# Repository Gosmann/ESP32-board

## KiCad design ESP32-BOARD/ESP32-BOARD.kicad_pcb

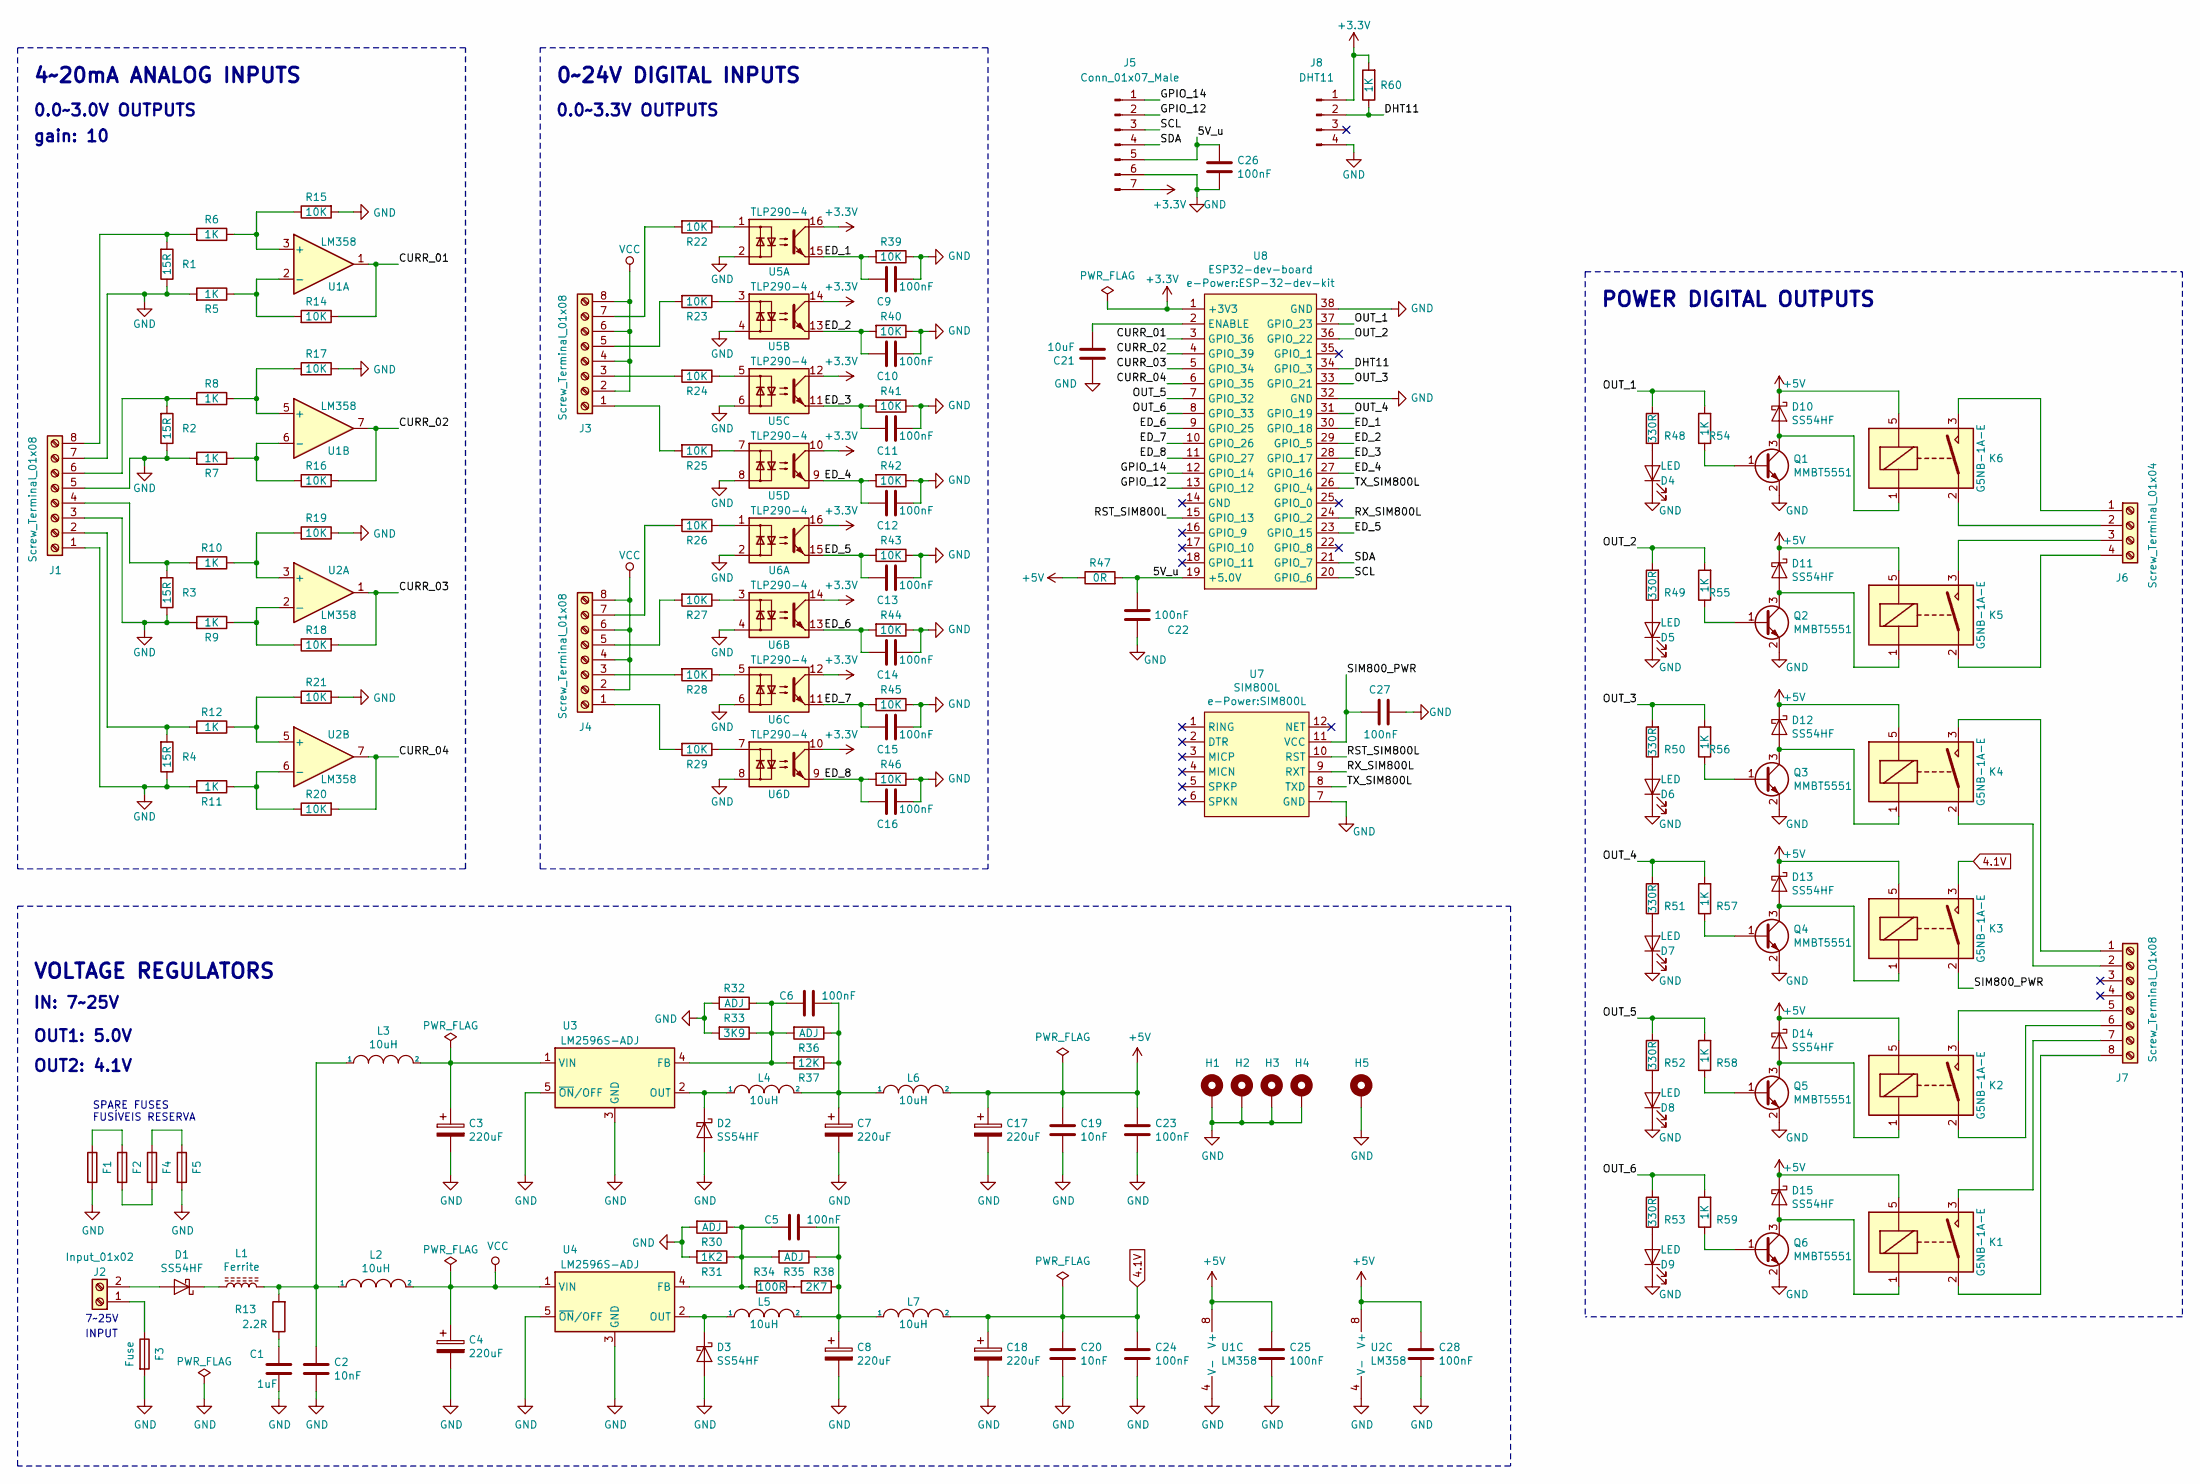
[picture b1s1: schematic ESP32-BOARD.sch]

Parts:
C1: 1uF; C_0805_2012Metric; LCSC C28323
C2, C19, C20: 10nF; C_0805_2012Metric; LCSC C1710
C3, C4, C7, C8, C17, C18: 220uF; CP_Elec_8x10; LCSC C311611
C5, C6, C9, C10, C11, C12, C13, C14, C15, C16, C22, C23, C24, C25, C26, C27, C28: 100nF; C_0805_2012Metric; LCSC C49678
C21: 10uF; C_0805_2012Metric; LCSC C15850
D1, D2, D3, D10, D11, D12, D13, D14, D15: SS54HF; DO-214AC; LCSC C22452
D4, D5, D6, D7, D8, D9: LED; LED_0805_2012Metric; LCSC C84256
F1, F2, F3, F4, F5: Fuse; FUSE_1206_3216Metric; LCSC C182445
H1, H2, H3, H4: MountingHole_Pad; MountingHole_4mm_Pad_Via
H5: MountingHole_Pad; MountingHole_3.2mm_M3_Pad
J1, J3, J4, J7: Screw_Terminal_01x08; TerminalBlock_Phoenix_MKDS-1,5-8-5.08_1x08_P5.08mm_Horizont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
J2: Input_01x02; TerminalBlock_Phoenix_MKDS-1,5-2_1x02_P5.00mm_Horizontal
J5: Conn_01x07_Male; PinHeader_1x07_P2.54mm_Horizontal
J6: Screw_Terminal_01x04; TerminalBlock_Phoenix_MKDS-1,5-4-5.08_1x04_P5.08mm_Horizont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
J8: DHT11; PinHeader_1x04_P2.54mm_Vertical
K1, K2, K3, K4, K5, K6: G5NB-1A-E; Relay_SPST_Omron-G5Q-1A
L1: Ferrite; FB_0603_1608Metric; LCSC C1002
L2, L3, L4, L5, L6, L7: 10uH; L_10.4x10.4_H4.8; LCSC C9935
Q1, Q2, Q3, Q4, Q5, Q6: MMBT5551; SOT-23; LCSC C2145
R1, R2, R3, R4: 15R; R_0805_2012Metric; LCSC C17480
R5, R6, R7, R8, R9, R10, R11, R12, R54, R55, R56, R57, R58, R59, R60: 1K; R_0805_2012Metric; LCSC C17513
R13: 2.2R; R_0805_2012Metric; LCSC C17521
R14, R15, R16, R17, R18, R19, R20, R21, R22, R23, R24, R25, R26, R27, R28, R29, R39, R40, R41, R42, R43, R44, R45, R46: 10K; R_0805_2012Metric; LCSC C17414
R30, R32, R35, R36: ADJ; R_0805_2012Metric
R31: 1K2; R_0805_2012Metric; LCSC C17379
R33: 3K9; R_0805_2012Metric; LCSC C17614
R34: 100R; R_0805_2012Metric; LCSC C17408
R37: 12K; R_0805_2012Metric; LCSC C17444
R38: 2K7; R_0805_2012Metric; LCSC C17530
R47: 0R; R_0805_2012Metric; LCSC C17477
R48, R49, R50, R51, R52, R53: 330R; R_0805_2012Metric; LCSC C17630
U1, U2: LM358; SOIC-8_3.9x4.9mm_P1.27mm; LCSC C7950
U3, U4: LM2596S-ADJ; TO-263-5_TabPin3; LCSC C52684
U5, U6: TLP290-4; SOIC-16_4.55x10.3mm_P1.27mm(TLP290-4); LCSC C39031
U7: SIM800L
U8: ESP32-dev-board; ESP-32-dev-kit

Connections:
4.1V: C18.1, C20.1, C24.1, K3.3, L7.2
+3V3: J5.7, J8.1, R60.2, U5.10, U5.12, U5.14, U5.16, U6.10, U6.12, U6.14, U6.16, U8.1 (+3V3)
+5V: C17.1, C19.1, C23.1, C25.1, C28.1, D10.1 (K), D11.1 (K), D12.1 (K), D13.1 (K), D14.1 (K), D15.1 (K), K1.5, K2.5, K3.5, K4.5, K5.5, K6.5, L6.2, R47.1, U1.8 (V+), U2.8 (V+)
/5V_u: C22.2, C26.1, J5.5, R47.2, U8.19 (+5.0V)
/CURR_01: R14.1, U1.1, U8.3 (GPIO_36)
/CURR_02: R16.2, U1.7, U8.4 (GPIO_39)
/CURR_03: R18.2, U2.1, U8.5 (GPIO_34)
/CURR_04: R20.2, U2.7, U8.6 (GPIO_35)
/DHT11: J8.2, R60.1, U8.34 (GPIO_3)
/ED_1: C9.2, R39.2, U5.15, U8.30 (GPIO_18)
/ED_2: C10.2, R40.2, U5.13, U8.29 (GPIO_5)
/ED_3: C11.2, R41.2, U5.11, U8.28 (GPIO_17)
/ED_4: C12.2, R42.2, U5.9, U8.27 (GPIO_16)
/ED_5: C13.2, R43.2, U6.15, U8.23 (GPIO_15)
/ED_6: C14.2, R44.2, U6.13, U8.9 (GPIO_25)
/ED_7: C15.2, R45.2, U6.11, U8.10 (GPIO_26)
/ED_8: C16.2, R46.2, U6.9, U8.11 (GPIO_27)
/GPIO_12: J5.2, U8.13 (GPIO_12)
/GPIO_14: J5.1, U8.12 (GPIO_14)
/OUT_1: R48.2, R54.2, U8.37 (GPIO_23)
/OUT_2: R49.2, R55.2, U8.36 (GPIO_22)
/OUT_3: R50.2, R56.2, U8.33 (GPIO_21)
/OUT_4: R51.2, R57.2, U8.31 (GPIO_19)
/OUT_5: R52.2, R58.2, U8.7 (GPIO_32)
/OUT_6: R53.2, R59.2, U8.8 (GPIO_33)
/RST_SIM800L: U7.10 (RST), U8.15 (GPIO_13)
/RX_SIM800L: U7.9 (RXT), U8.24 (GPIO_2)
/SCL: J5.3, U8.20 (GPIO_6)
/SDA: J5.4, U8.21 (GPIO_7)
/SIM800_PWR: C27.1, K3.2, U7.11 (VCC)
/TX_SIM800L: U7.8 (TXD), U8.26 (GPIO_4)
GND: C1.2, C2.2, C3.2, C4.2, C7.2, C8.2, C9.1, C10.1, C11.1, C12.1, C13.1, C14.1, C15.1, C16.1, C17.2, C18.2, C19.2, C20.2, C21.1, C22.1, C23.2, C24.2, C25.2, C26.2, C27.2, C28.2, D2.2 (A), D3.2 (A), D4.1 (K), D5.1 (K), D6.1 (K), D7.1 (K), D8.1 (K), D9.1 (K), F1.2, F3.2, F5.2, H1.1, H2.1, H3.1, H4.1, H5.1, J1.1, J1.3, J1.5, J1.7, J5.6, J8.4, Q1.2 (E), Q2.2 (E), Q3.2 (E), Q4.2 (E), Q5.2 (E), Q6.2 (E), R1.1, R2.1, R3.1, R4.1, R5.2, R7.2, R9.2, R11.2, R15.2, R17.1, R19.1, R21.1, R30.2, R31.2, R32.2, R33.2, R39.1, R40.1, R41.1, R42.1, R43.1, R44.1, R45.1, R46.1, U1.4 (V-), U2.4 (V-), U3.3 (GND), U3.5 (~ON~/OFF), U4.3 (GND), U4.5 (~ON~/OFF), U5.2, U5.4, U5.6, U5.8, U6.2, U6.4, U6.6, U6.8, U7.7 (GND), U8.32 (GND), U8.38 (GND)
unnamed: C1.1, R13.1
unnamed: C2.1, L1.2, L2.1, L3.1, R13.2
unnamed: C3.1, L3.2, U3.1 (VIN)
unnamed: C5.1, C8.1, L5.2, L7.1, R35.1, R38.1
unnamed: C5.2, R30.1, R31.1, R34.2, R35.2, U4.4 (FB)
unnamed: C6.1, C7.1, L4.2, L6.1, R36.1, R37.1
unnamed: C6.2, R32.1, R33.1, R36.2, R37.2, U3.4 (FB)
unnamed: C21.2, U8.2 (ENABLE)
unnamed: D1.1 (K), L1.1
unnamed: D1.2 (A), J2.2
unnamed: D2.1 (K), L4.1, U3.2 (OUT)
unnamed: D3.1 (K), L5.1, U4.2 (OUT)
unnamed: D4.2 (A), R48.1
unnamed: D5.2 (A), R49.1
unnamed: D6.2 (A), R50.1
unnamed: D7.2 (A), R51.1
unnamed: D8.2 (A), R52.1
unnamed: D9.2 (A), R53.1
unnamed: D10.2 (A), K6.1, Q1.3 (C)
unnamed: D11.2 (A), K5.1, Q2.3 (C)
unnamed: D12.2 (A), K4.1, Q3.3 (C)
unnamed: D13.2 (A), K3.1, Q4.3 (C)
unnamed: D14.2 (A), K2.1, Q5.3 (C)
unnamed: D15.2 (A), K1.1, Q6.3 (C)
unnamed: F1.1, F2.1
unnamed: F2.2, F4.2
unnamed: F3.1, J2.1
unnamed: F4.1, F5.1
unnamed: J1.2, R4.2, R12.2
unnamed: J1.4, R3.2, R10.2
unnamed: J1.6, R2.2, R8.2
unnamed: J1.8, R1.2, R6.2
unnamed: J3.1, R25.2
unnamed: J3.3, R24.2
unnamed: J3.5, R23.2
unnamed: J3.7, R22.2
unnamed: J4.1, R29.2
unnamed: J4.3, R28.2
unnamed: J4.5, R27.2
unnamed: J4.7, R26.2
unnamed: J6.1, K6.3
unnamed: J6.2, K6.2
unnamed: J6.3, K5.3
unnamed: J6.4, K5.2
unnamed: J7.1, K4.3
unnamed: J7.2, K4.2
unnamed: J7.5, K2.3
unnamed: J7.6, K2.2
unnamed: J7.7, K1.3
unnamed: J7.8, K1.2
unnamed: Q1.1 (B), R54.1
unnamed: Q2.1 (B), R55.1
unnamed: Q3.1 (B), R56.1
unnamed: Q4.1 (B), R57.1
unnamed: Q5.1 (B), R58.1
unnamed: Q6.1 (B), R59.1
unnamed: R10.1, R19.2, U2.3 (+)
unnamed: R11.1, R20.1, U2.6 (-)
unnamed: R12.1, R21.2, U2.5 (+)
unnamed: R5.1, R14.2, U1.2 (-)
unnamed: R6.1, R15.1, U1.3 (+)
unnamed: R7.1, R16.1, U1.6 (-)
unnamed: R8.1, R17.2, U1.5 (+)
unnamed: R9.1, R18.1, U2.2 (-)
unnamed: R22.1, U5.1
unnamed: R23.1, U5.3
unnamed: R24.1, U5.5
unnamed: R25.1, U5.7
unnamed: R26.1, U6.1
unnamed: R27.1, U6.3
unnamed: R28.1, U6.5
unnamed: R29.1, U6.7
unnamed: R34.1, R38.2
VCC: C4.1, J3.2, J3.4, J3.6, J3.8, J4.2, J4.4, J4.6, J4.8, L2.2, U4.1 (VIN)

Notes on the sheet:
VOLTAGE REGULATORS
IN: 7~~25V
OUT1: 5.0V
OUT2: 4.1V
4~~20mA ANALOG INPUTS
0~~24V DIGITAL INPUTS
0.0~~3.3V OUTPUTS
POWER DIGITAL OUTPUTS
0.0~~3.0V OUTPUTS
gain: 10
INPUT
7~~25V
SPARE FUSES FUSÍVEIS RESERVA

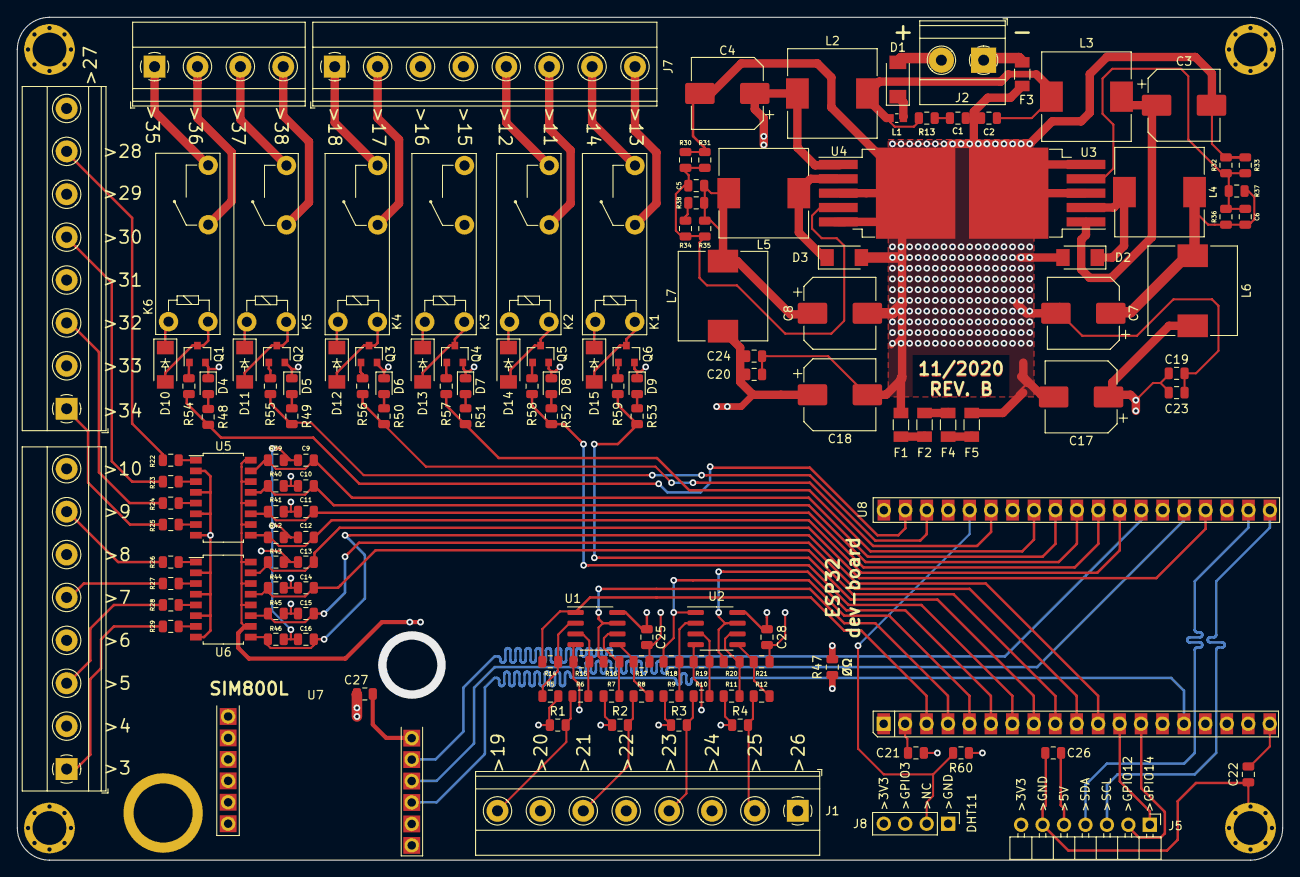
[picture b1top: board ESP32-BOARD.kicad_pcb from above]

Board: 4 copper layers, 149.9 x 99.8 mm, 148 parts (0 on the bottom side), 106 nets.

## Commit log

2020-07-25 added files to the repo
2020-07-26 changes made on the analog inputs
2020-07-26 arrumei as dimensoes dos furos
2020-07-26 changes de boards to 4 layers
2020-07-28 updates related to review B
2020-07-28 added 3d models
2020-07-28 changes have been made
2020-07-28 update on project
2020-10-14 modificacoes na placa
2020-10-21 atualizacao placa
2020-11-04 update gerbers and production files
